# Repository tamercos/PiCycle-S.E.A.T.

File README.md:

# PiCycle S.E.A.T.
The PiCycle S.E.A.T. (Situational and Environmental Awareness Technology) aims to combine ultrasonic sensors with a Raspberry Pi utilising haptic feedback with the objective of increasing road safety for cyclists.

HC-SR04 ultrasonic sensors placed under the seat of the bicycle facing backwards will detect the approach of foreign objects and alert the cyclist via small vibration motors situated within the rider's helmet.

The system will increase road safety for bicycle users by allowing them to 'feel' what they cannot see behind them. Current solutions rely on wearable mirrors as wrist bands. These force cyclists to take their eyes off the road infront creating more potential dangers. The PiCycle S.E.A.T enables continuous blind spot observation without distracting the cyclist.

**A short video demonstrating the device prototype can be found here:**

https://www.youtube.com/watch?v=8pkJoHdxL40&feature=youtu.be

## Parts Used
The list below highlights some of the key hardware needed to replicate this project. Please note that circuit components can be found in the circuit schematic. A full list of this hardware with cost at time of completion is also given in "Project Components and Expenditure.xlsx"

- 3x HC-SR04 ultrasonic sensors
- 3x Seed mini vibration motor 3V 2.0mm circular
- 3D printed parts found under the "PiCycleSEAT 3D Print" folder
- 5x M2.5 x 8mm screws for the housing lid
- 4x M2.5 x 6mm screws for Raspberry Pi
- 1x Makibes Touch Screen 3.5" Resistive LCD
- 1x Long pin stack header
- 1x Perma-proto hat for Raspberry Pi Adafruit Perma-Proto Pi HAT!
- 1x 26 connection ribbon cable
- 5x 6 Way Straight Pin Header
- 1x Cable Mount IDC Connector

## Circuitry Used
The system is fully powered from the Raspberry Pi.

## System Diagram

## Social Media
We are delighted to share with you our Twitter page. You can follow all of our up to date news on the project there:

https://twitter.com/The_PiCycle

Check out our page and follow us :) 

Enjoy!

# ...Check out our Wiki for more project details and help...

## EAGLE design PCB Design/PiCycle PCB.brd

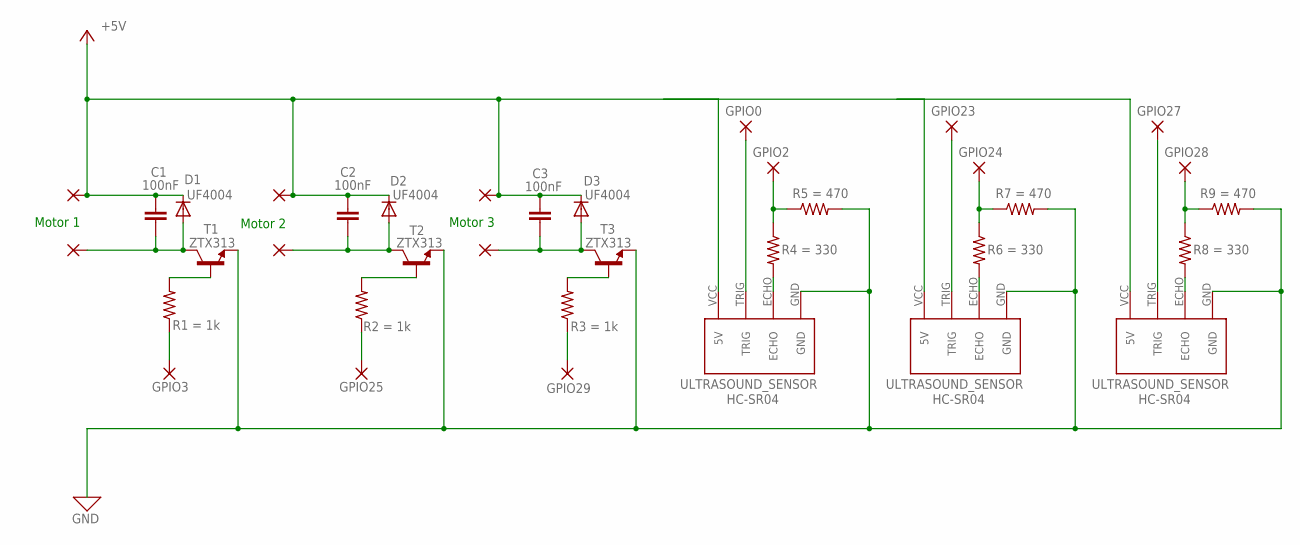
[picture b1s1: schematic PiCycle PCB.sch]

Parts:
C1, C2, C3: C15/6; C15B6
D1, D2, D3: BA243A; DO35-10
J_ULTRASONIC_1, J_ULTRASONIC_2, J_ULTRASONIC_3: HC-SR04; HC-SR04_FOOTPRINT
PAD1, PAD2, PAD3, PAD4, PAD5, PAD6, PAD7, PAD8, PAD9, PAD10, PAD11, PAD12, PAD13, PAD14, PAD15: 3,81/1,4
R1, R2, R3, R4, R5, R6, R7, R8, R9: R-US_0207/15; 0207/15
T1, T2, T3: 2N706; TO18

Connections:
0: J_ULTRASONIC_1.GND, J_ULTRASONIC_2.GND, J_ULTRASONIC_3.GND, R5.2, R7.2, R9.2, T1.1 (E), T2.1 (E), T3.1 (E)
+5V: C1.1, C2.1, C3.1, D1.C, D2.C, D3.C, J_ULTRASONIC_1.VCC (5V), PAD5.1, PAD6.1, PAD9.1
+5V1: J_ULTRASONIC_2.VCC (5V)
+5V2: J_ULTRASONIC_3.VCC (5V)
unnamed: PAD1.1, R1.1
unnamed: PAD2.1, R2.1
unnamed: PAD3.1, R3.1
unnamed: R1.2, T1.2 (B)
unnamed: R2.2, T2.2 (B)
unnamed: R3.2, T3.2 (B)
unnamed: C1.2, D1.A, PAD4.1, T1.3 (C)
unnamed: C2.2, D2.A, PAD7.1, T2.3 (C)
unnamed: C3.2, D3.A, PAD8.1, T3.3 (C)
unnamed: J_ULTRASONIC_2.TRIG, PAD10.1
unnamed: J_ULTRASONIC_1.TRIG, PAD11.1
unnamed: J_ULTRASONIC_2.ECHO, R4.2
unnamed: J_ULTRASONIC_1.ECHO, R8.2
unnamed: PAD15.1, R8.1, R9.1
unnamed: PAD12.1, R4.1, R5.1
unnamed: J_ULTRASONIC_3.TRIG, PAD13.1
unnamed: J_ULTRASONIC_3.ECHO, R6.2
unnamed: PAD14.1, R6.1, R7.1

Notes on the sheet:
Motor 1
Motor 2
Motor 3

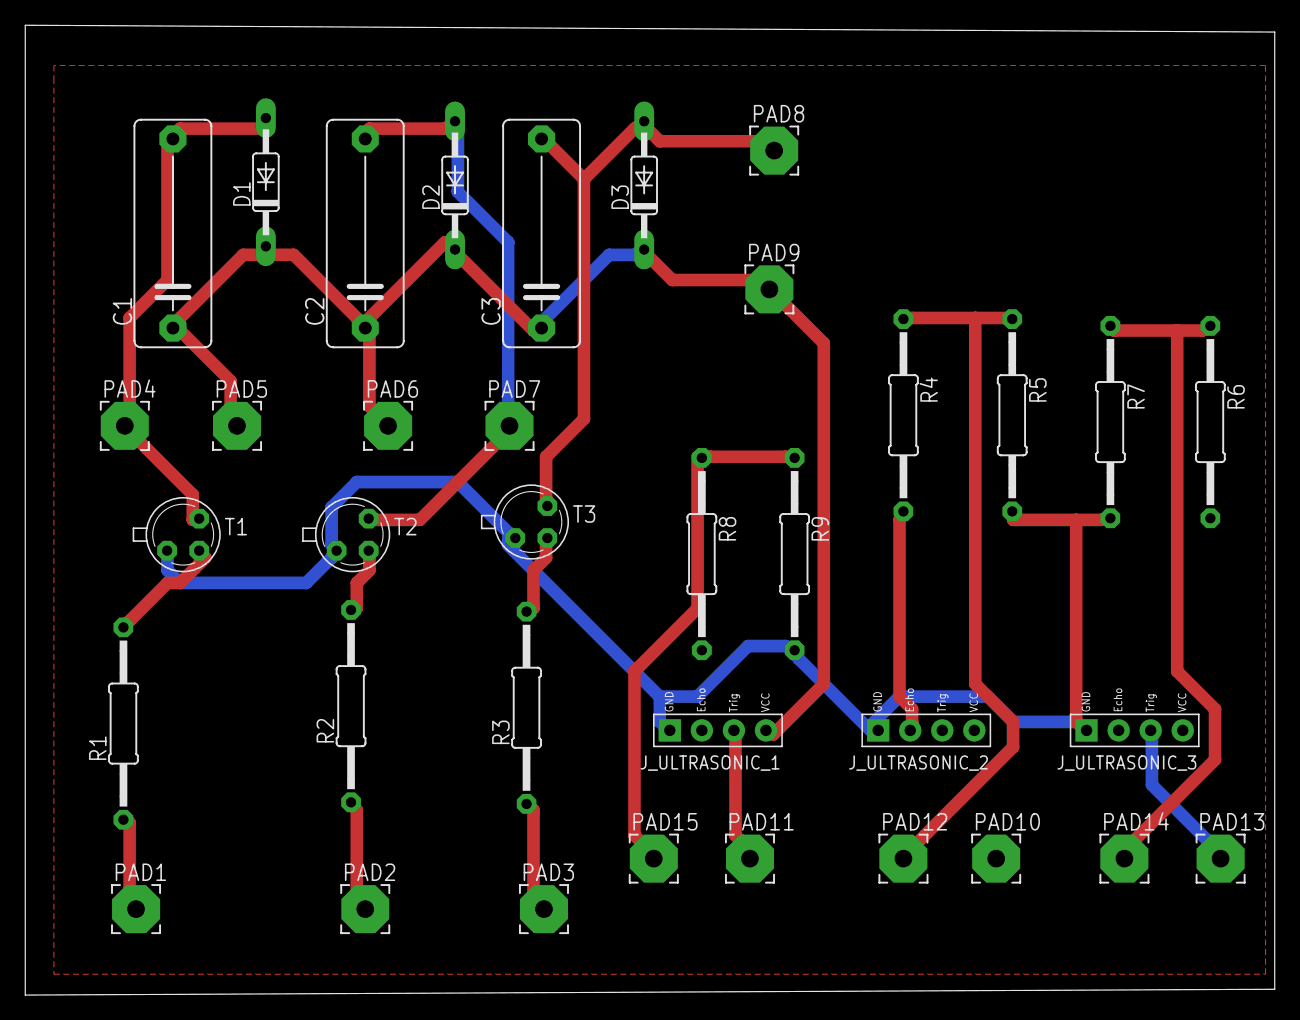
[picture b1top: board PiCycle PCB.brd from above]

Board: 2 copper layers, 99.0 x 76.8 mm, 36 parts (0 on the bottom side), 20 nets.

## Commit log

2018-01-18 Sample code
    Made a quick "hello world" varient to test out github
2018-01-18 Set theme jekyll-theme-midnight
2018-01-18 messing about
2018-01-18 night night
2018-01-18 added a comment (still practicing with github)
2018-01-18 Broken yo file
2018-01-18 fixed it
2018-01-18 Made it More complicated
2018-01-18 changes v2
2018-01-18 main v2.1
2018-01-18 Removed unused files
2018-01-18 Renamed for convention
2018-01-24 Example of using GitHub for Li
2018-01-24 led blinker added
2018-01-31 Motor stuff
2018-02-06 Motor code update
    Using wiringPi library to address gpio. This fixes bug where the programme requires to be interupted for subsequent runs to be succesful.
2018-02-07 Add files via upload
    code for ultrasonic sensor
2018-02-07 Add files via upload
    on website
    https://ninedof.wordpress.com/2013/07/16/rpi-hc-sr04-ultrasonic-sensor-mini-project/
2018-02-07 code 3
2018-02-13 cleanup
2018-02-14 Presentation
2018-02-15 Early Code for Ultrasound working with motors
    We reached reading data from 2 ultrasound sensors simultaneously but could not trigger the motors independantly yet.
    May be issue with the physical circuitry or a small bug in the software.
2018-02-15 Updated code. Motors run Independantly with third motor activating when motors 1 and 2 are on
    The previous version of the code was fine but we had a fault with the circuitry that was causing the vibrating motors to all drive at the same time. This problem has been resolved. The new code is a 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
2018-02-22 PiCycle SEAT
    Added code for three sonars and motors to function independantly
2018-02-22 V1.3
    - Programme now displays 2 decimal places.
    - Huge clean-up. Removed all unnecessary and redundant files.
2018-03-01 Added instructions to run programme
2018-03-01 Clean-up
    Removed more unnecessary files
2018-03-01 Updated instructions
2018-03-01 3D printed parts that are used in this project
2018-03-01 Updated parts list
2018-03-07 Bug fix
    Fixed a bug where pinMode was not declaring INPUT/OUTPUT correctly
2018-03-14 Updated .stl files
    There was an oversight when exporting the .stl files where the component would be 10x smaller than desired. This has now been accounted for.
2018-03-14 Minor changes
    Added simple option to change sample rate in code as well as some other small changes
2018-03-15 Qt template added
2018-03-16 W.I.P.
    Currently disfunctional
2018-03-21 v1.1 Circuitry
    Early schematic. Component names and values to be added/tidied. Connector pad labels to be added.
    .sch and .brd files will be added at a later date
2018-03-21 V2.0
    Minimum viable product of code running with GUI now functional. A spinbox to vary the detection range of the sensors has been added.
    This is the absolute bare minimum for the GUI in its current state. Implementation of further GUI elements to come.
2018-03-22 CAD model drawings available as PDFs
2018-03-23 Removing old circuit
    Circuit with wrong component names and untidy layout
2018-03-23 Circuit diagram
    New v1.2 is an updated circuit with correct component names and values. As working prototype.
    Generally neater layout
2018-03-23 Circuit PNG
    For Readme
2018-03-23 Circuit Diagram to readme
    added general schematic to readme file
2018-03-23 EAGLE .sch file
    .sch file of circuit can be opened and edited using EAGLE
2018-03-23 Adding images to use in wiki
2018-03-23 New Table of Connections image
    Old image was a photo of computer screen. Was able to find an official table from manufacturer
2018-03-23 Some Images of our initial stages in prototyping
    Enjoy!
2018-03-23 System Flow Chart
    A high level diagram of the system
2018-03-23 V2.1
    - Replaced spinbox with scrollbar for setting the detection range of the senors.
    - Added checkboxes to activate/deactivate select vibration discs
    - cleanup
2018-03-25 V2.2
    - Additional comments added to code for clarity
    - Folder structure reorganised for clarity
    - Bug fix: disabling a vibration disc in the UI would actually just freeze its last state (i.e. if the vibration disc was ON when "disabled" then vibration would persist perpetually). This bug has no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
2018-03-28 V2.3
    - Optimised GUI layout for 3.5inch touchscreen
    - Added additional label to GUI for clarity
2018-04-04 disappeared circuit diagram replaced in readme file
2018-04-04 Operation of the ultrasound sensor
2018-04-04 Images and videos of prototype
2018-04-04 Prototype Stages
    Before the system is wireless, we have a nice prototype of the vibration discs fixed to the inner band of a bicycle helmet
2018-04-05 A list of the components purchased and used
    Here you can find all the items needed for this project and the cost (05/04/2018)
2018-04-05 FLow Chart of System
    Highlighting the processes and comms method
2018-04-05 Flow chart of system
2018-04-09 PCB Design Files
    Here we have the files to open the PCB on Eagle. If you don't have this program then feel free to just use the PDF files. The back surface of the PCB has been mirrored already and fully ready for pri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
2018-04-11 List of Components for this project and cost
    update in file disclaimer
2018-04-11 READ ME
    updated social media links
2018-04-11 Read Me
    update to direct reader to wiki page for help and advice
2018-04-11 V2.4
    Bug fix where variables were not initialised properly
2018-04-12 License
2018-04-14 README
    Included youtube link to prototype demonstration
